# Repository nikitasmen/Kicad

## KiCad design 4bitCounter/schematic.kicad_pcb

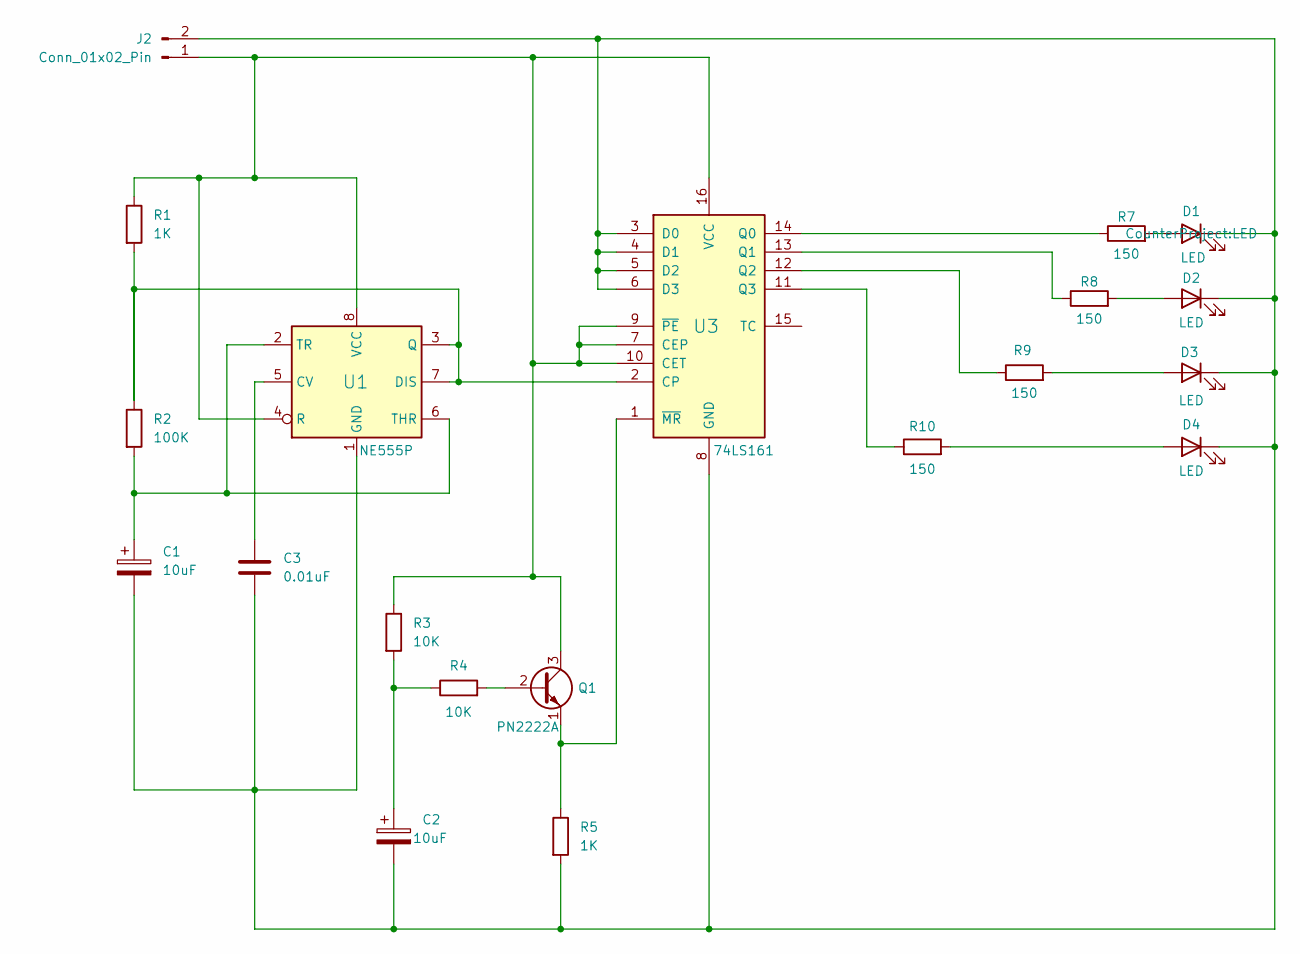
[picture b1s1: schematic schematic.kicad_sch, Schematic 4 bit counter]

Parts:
C1, C2: 10uF; Capacitor
C3: 0.01uF; Capacitor
D1, D2, D3, D4: LED
J2: Conn_01x02_Pin; Connector
Q1: PN2222A; Transistor
R1, R5: 1K; Resistor
R2: 100K; Resistor
R3, R4: 10K; Resistor
R7, R8, R9, R10: 150; Resistor
U1: NE555P; Timer
U3: 74LS161; CounterChip

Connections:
unnamed: C2.1, R3.2, R4.1
unnamed: D1.2 (A), R7.2
unnamed: C1.2, C2.2, C3.2, D1.1 (K), D2.1 (K), D3.1 (K), D4.1 (K), J2.2, R5.2, U1.1 (GND), U3.3 (D0), U3.4 (D1), U3.5 (D2), U3.6 (D3), U3.8 (GND)
unnamed: D2.2 (A), R8.2
unnamed: D3.2 (A), R9.2
unnamed: D4.2 (A), R10.2
unnamed: J2.1, Q1.3 (C), R1.1, R3.1, U1.4 (R), U1.8 (VCC), U3.7 (CEP), U3.9 (~PE), U3.10 (CET), U3.16 (VCC)
unnamed: Q1.2 (B), R4.2
unnamed: Q1.1 (E), R5.1, U3.1 (~MR)
unnamed: C3.1, U1.5 (CV)
unnamed: R1.2, R2.1, U1.3 (Q), U1.7 (DIS), U3.2 (CP)
unnamed: C1.1, R2.2, U1.2 (TR), U1.6 (THR)
unnamed: R7.1, U3.14 (Q0)
unnamed: R8.1, U3.13 (Q1)
unnamed: R9.1, U3.12 (Q2)
unnamed: R10.1, U3.11 (Q3)

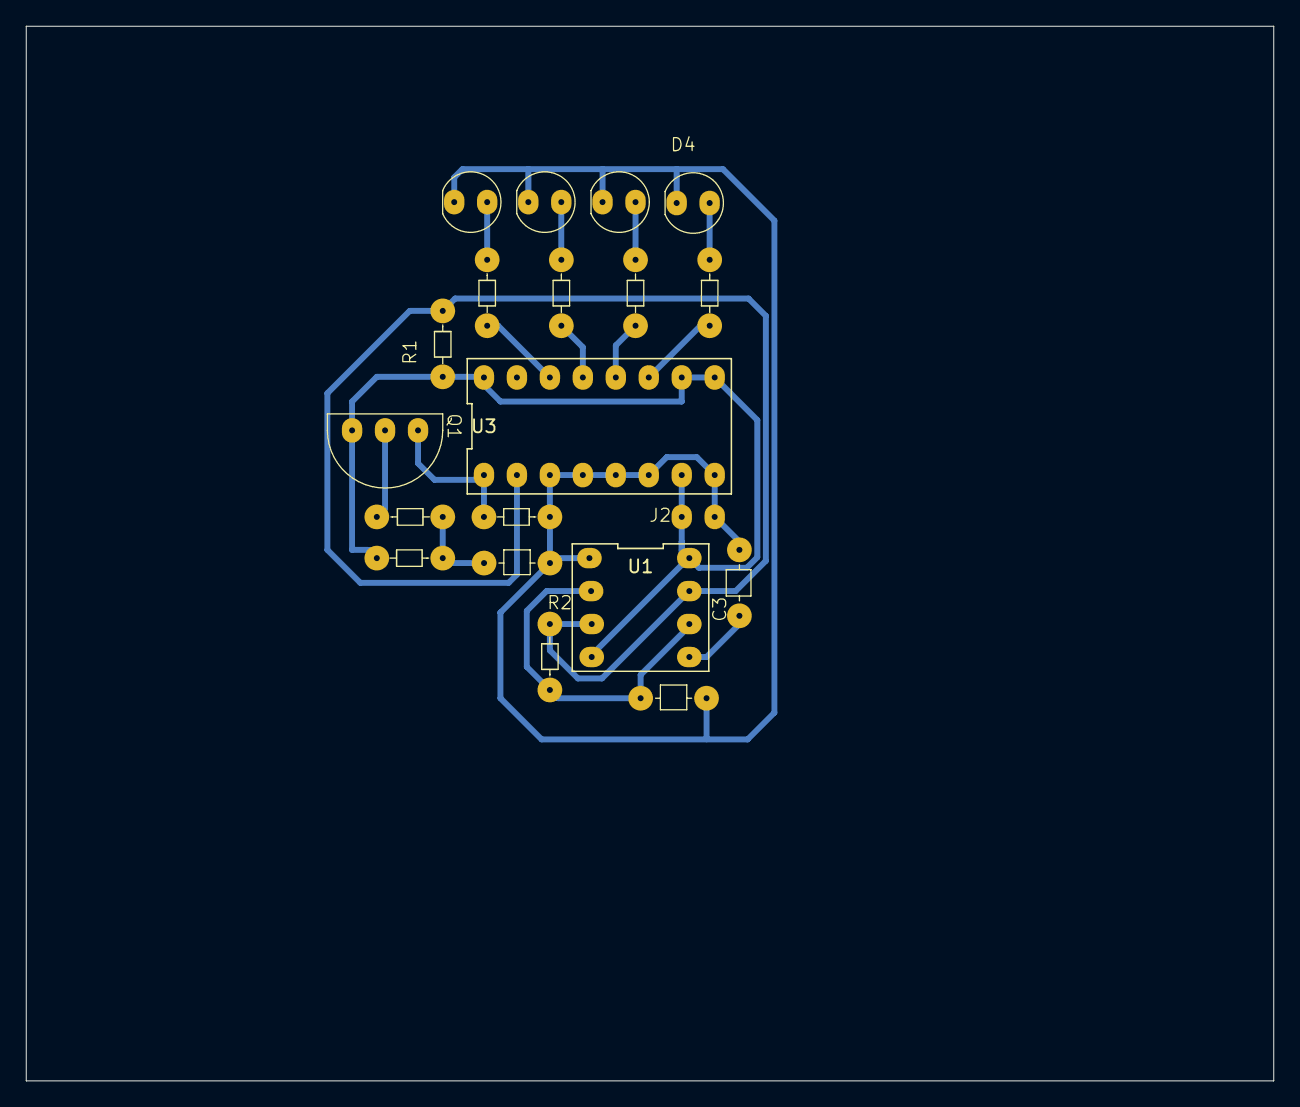
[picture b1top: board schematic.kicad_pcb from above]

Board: 2 copper layers, 96.1 x 81.3 mm, 20 parts (0 on the bottom side), 16 nets.

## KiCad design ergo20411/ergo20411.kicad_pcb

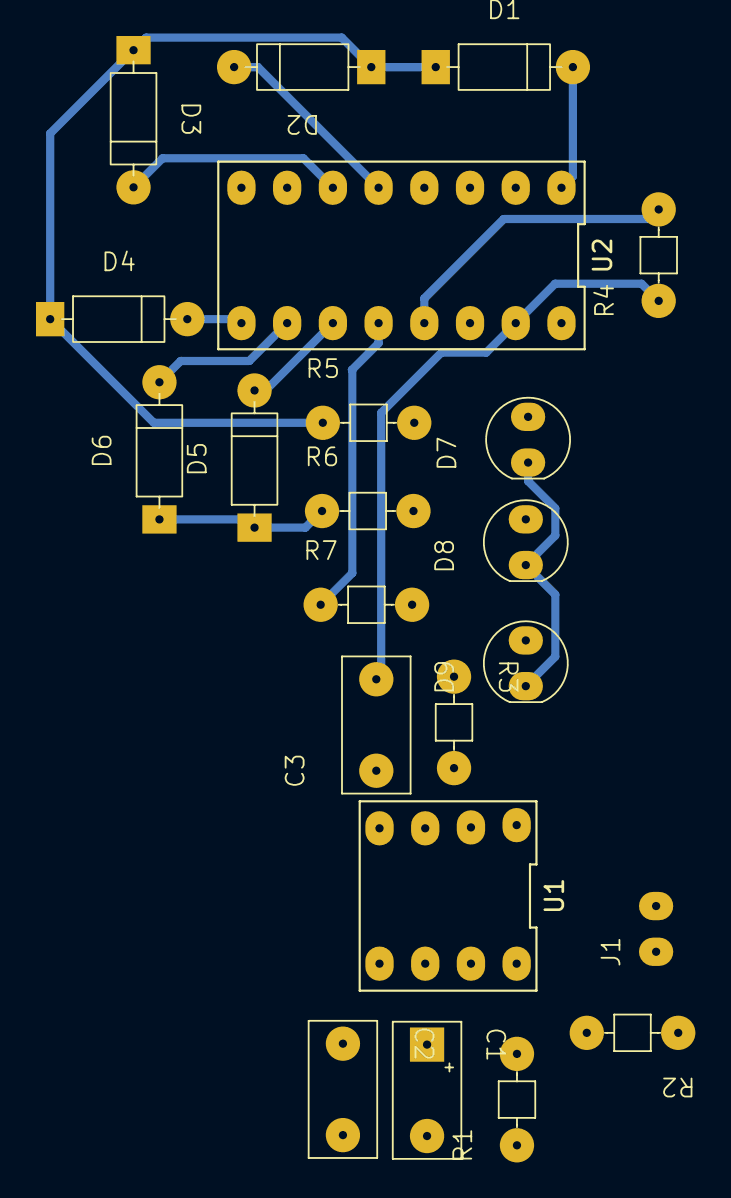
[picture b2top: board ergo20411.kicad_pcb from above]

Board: 2 copper layers, 22 parts (0 on the bottom side), 21 nets.

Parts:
C1: 47u; CP
C2: 0.01uF; Capacitor
C3: 6.8nF; Capacitor
D1, D2, D3, D4, D5, D6: 1N4148; Diode
D7: LED-GREEN; LED
D8: LED-YELLOW; LED
D9: LED-RED; LED
J1: Conn_01x02_Pin; Connector
R1, R3: 10k; Resistor
R2: 22k; Resistor
R4: 100k; Resistor
R5, R6, R7: 100R; Resistor
U1: LM555xN; 555
U2: 4017; Counter

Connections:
GND: C1.2, C2.2, D7.1 (K), D8.1 (K), D9.1 (K), J1.2, U1.1 (GND)
unnamed: D1.2 (A), U2.1 (Q5)
unnamed: D1.1 (K), D2.1 (K), D3.1 (K), D4.1 (K), R5.1
unnamed: D2.2 (A), U2.5 (Q6)
unnamed: D3.2 (A), U2.6 (Q7)
unnamed: D4.2 (A), U2.9 (Q8)
unnamed: D5.2 (A), U2.11 (Q9)
unnamed: D5.1 (K), D6.1 (K), R6.1
unnamed: D6.2 (A), U2.10 (Q4)
unnamed: D7.2 (A), R5.2
unnamed: D8.2 (A), R6.2
unnamed: D9.2 (A), R7.2
unnamed: C3.1, J1.1, R2.1, U1.4 (R), U1.8 (VCC)
unnamed: C2.1, U1.5 (CV)
unnamed: R1.1, R2.2, U1.7 (DIS)
unnamed: R3.2, U1.3 (Q)
unnamed: C1.1, R1.2, U1.2 (TR), U1.6 (THR)
unnamed: R4.2, U2.13 (CKEN)
unnamed: R3.1, U2.14 (CLK)
unnamed: R7.1, U2.12 (Cout)
unnamed: C3.2, R4.1, U2.15 (Reset)

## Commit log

2024-10-12 Project Chantzakis intial
2024-12-01 Updates on footprints and schematic
2024-12-01 Remove project
2024-12-03 Update footprints and pcb
2024-12-10 Update pcb schematic
2024-12-10 Update pcb
2024-12-15 Update pcb routing
2024-12-17 update pcb and schematic
2025-01-08 Update 4 bit counter
2025-01-08 Add initial ergo20411
